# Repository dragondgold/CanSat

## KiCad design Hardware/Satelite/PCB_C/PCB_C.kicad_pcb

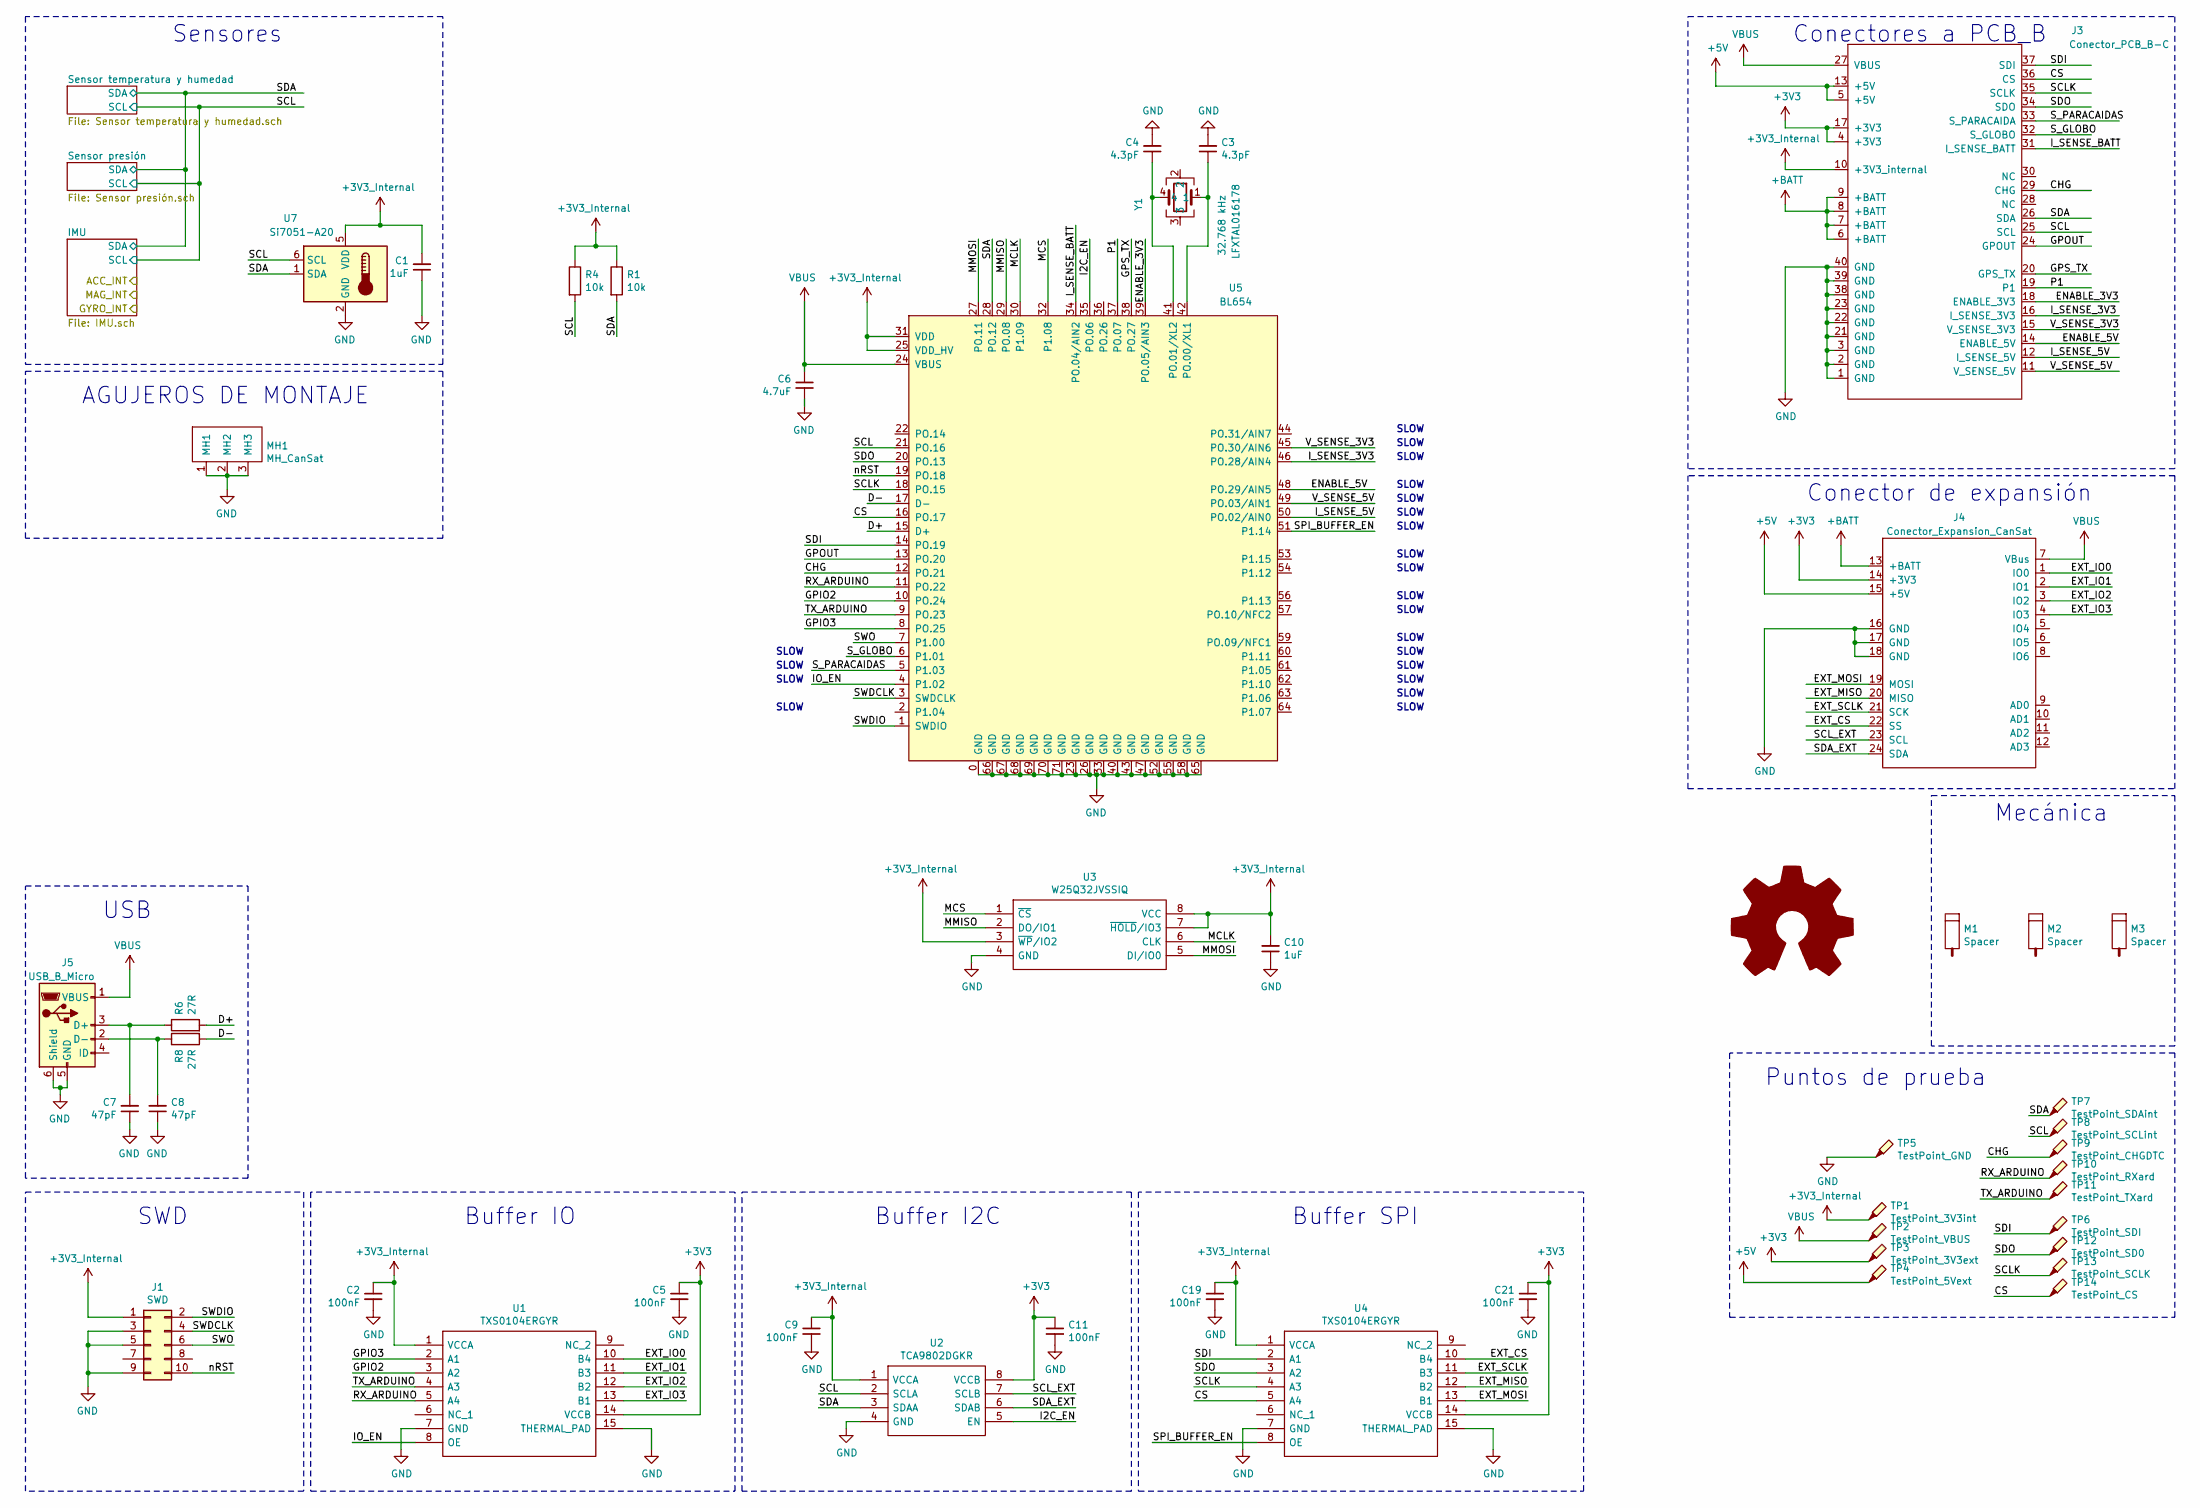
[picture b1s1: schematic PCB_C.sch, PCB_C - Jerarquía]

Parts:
C1, C10: 1uF; C_0402_1005Metric; Manufacturer Part Number GRM155R61E105KA12D
C2, C5, C9, C11, C19, C21: 100nF; C_0402_1005Metric; Manufacturer Part Number GCM155R71C104KA55D
C3, C4: 4.3pF; C_0402_1005Metric; Manufacturer Part Number GRM1555C1H4R3WA01D
C6: 4.7uF; C_0805_2012Metric_Pad1.15x1.40mm_HandSolder; Manufacturer Part Number GRM21BR71A475KE51K
C7, C8: 47pF; C_0402_1005Metric; Manufacturer Part Number AC0402JRNPO9BN470
J1: SWD; PinHeader_2x05_P1.27mm_Vertical_SMD; Manufacturer Part Number 20021121-00010D4LF
J3: Conector_PCB_B-C; Conector_PCB_B-C_Lado_C; Manufacturer Part Number 53353-1071
J4: Conector_Expansion_CanSat; Manufacturer Part Number SSQ-106-03-T-S
J5: USB_B_Micro; USB_Micro-B_Molex_47346-0001; Manufacturer Part Number 47346-1001
M1, M2, M3: Spacer; Empty_Footprint; Manufacturer Part Number R30-3010702
MH1: MH_CanSat
R1, R4: 10k; R_0603_1608Metric_Pad1.05x0.95mm_HandSolder; Manufacturer Part Number RC0603JR-0710KL
R6, R8: 27R; R_0603_1608Metric_Pad1.05x0.95mm_HandSolder; Manufacturer Part Number RC0603FR-0727RL
TP1: TestPoint_3V3int; TestPoint_Pad_D1.5mm
TP2: TestPoint_VBUS; TestPoint_Pad_D1.5mm
TP3: TestPoint_3V3ext; TestPoint_Pad_D1.5mm
TP4: TestPoint_5Vext; TestPoint_Pad_D1.5mm
TP5: TestPoint_GND; TestPoint_THTPad_1.5x1.5mm_Drill0.7mm
TP6: TestPoint_SDI; TestPoint_Pad_D1.5mm
TP7: TestPoint_SDAint; TestPoint_Pad_D1.5mm
TP8: TestPoint_SCLint; TestPoint_Pad_D1.5mm
TP9: TestPoint_CHGDTC; TestPoint_Pad_D1.5mm
TP10: TestPoint_RXard; TestPoint_Pad_D1.5mm
TP11: TestPoint_TXard; TestPoint_Pad_D1.5mm
TP12: TestPoint_SD0; TestPoint_Pad_D1.5mm
TP13: TestPoint_SCLK; TestPoint_Pad_D1.5mm
TP14: TestPoint_CS; TestPoint_Pad_D1.5mm
U1, U4: TXS0104ERGYR; Texas_S-PVQFN-N14; Manufacturer Part Number TXS0104ERGYR
U2: TCA9802DGKR; SOP65P490X110-8N; Manufacturer Part Number TCA9802DGKR
U3: W25Q32JVSSIQ; SOIC-8_3.9x4.9mm_P1.27mm; Manufacturer Part Number W25Q32JVSSIQ
U5: BL654; 45100001; Manufacturer Part Number 451-00002
U7: Si7051-A20; DFN-6-1EP_3x3mm_P1mm_EP1.5x2.4mm; Manufacturer Part Number SI7051-A20-IM
Y1: LFXTAL016178; LFXTAL016178_1; Manufacturer Part Number LFXTAL016178

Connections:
+3V3: C5.1, C11.1, C21.1, J3.4 (+3V3), J3.17 (+3V3), J4.14 (+3V3), TP3.1, U1.14 (VCCB), U2.8 (VCCB), U4.14 (VCCB)
+3V3_Internal: C1.2, C2.1, C9.1, C10.2, C19.1, J1.1, J3.10 (+3V3_internal), R1.1, R4.1, TP1.1, U1.1 (VCCA), U2.1 (VCCA), U3.3 (~WP~/IO2), U3.7 (~HOLD~/IO3), U3.8 (VCC), U4.1 (VCCA), U5.25 (VDD_HV), U5.31 (VDD), U7.5 (VDD); also elsewhere on the board
+5V: J3.5 (+5V), J3.13 (+5V), J4.15 (+5V), TP4.1
+BATT: J3.6 (+BATT), J3.7 (+BATT), J3.8 (+BATT), J3.9 (+BATT), J4.13 (+BATT)
/CHG: J3.29 (CHG), TP9.1, U5.12 (PO.21)
/CS: J3.36 (CS), TP14.1, U4.5 (A4), U5.16 (PO.17)
/D+: R6.2, U5.15 (D+)
/D-: R8.2, U5.17 (D-)
/ENABLE_3V3: J3.18 (ENABLE_3V3), U5.39 (PO.05/AIN3)
/ENABLE_5V: J3.14 (ENABLE_5V), U5.48 (PO.29/AIN5)
/EXT_CS: J4.22 (SS), U4.10 (B4)
/EXT_IO0: J4.1 (IO0), U1.10 (B4)
/EXT_IO1: J4.2 (IO1), U1.11 (B3)
/EXT_IO2: J4.3 (IO2), U1.12 (B2)
/EXT_IO3: J4.4 (IO3), U1.13 (B1)
/EXT_MISO: J4.20 (MISO), U4.12 (B2)
/EXT_MOSI: J4.19 (MOSI), U4.13 (B1)
/EXT_SCLK: J4.21 (SCK), U4.11 (B3)
/GPIO2: U1.3 (A2), U5.10 (PO.24)
/GPIO3: U1.2 (A1), U5.8 (PO.25)
/GPOUT: J3.24 (GPOUT), U5.13 (PO.20)
/GPS_TX: J3.20 (GPS_TX), U5.38 (PO.27)
/I2C_EN: U2.5 (EN), U5.35 (PO.06)
/IO_EN: U1.8 (OE), U5.4 (P1.02)
/I_SENSE_3V3: J3.16 (I_SENSE_3V3), U5.46 (PO.28/AIN4)
/I_SENSE_5V: J3.12 (I_SENSE_5V), U5.50 (PO.02/AIN0)
/I_SENSE_BATT: J3.31 (I_SENSE_BATT), U5.34 (PO.04/AIN2)
/MCLK: U3.6 (CLK), U5.30 (P1.09)
/MCS: U3.1 (~CS), U5.32 (P1.08)
/MMISO: U3.2 (DO/IO1), U5.29 (PO.08)
/MMOSI: U3.5 (DI/IO0), U5.27 (PO.11)
/P1: J3.19 (P1), U5.37 (PO.07)
/RX_ARDUINO: TP10.1, U1.5 (A4), U5.11 (PO.22)
/SCL: J3.25 (SCL), R4.2, TP8.1, U2.2 (SCLA), U5.21 (PO.16), U7.6 (SCL); also elsewhere on the board
/SCLK: J3.35 (SCLK), TP13.1, U4.4 (A3), U5.18 (PO.15)
/SCL_EXT: J4.23 (SCL), U2.7 (SCLB)
/SDA: J3.26 (SDA), R1.2, TP7.1, U2.3 (SDAA), U5.28 (PO.12), U7.1 (SDA); also elsewhere on the board
/SDA_EXT: J4.24 (SDA), U2.6 (SDAB)
/SDI: J3.37 (SDI), TP6.1, U4.2 (A1), U5.14 (PO.19)
/SDO: J3.34 (SDO), TP12.1, U4.3 (A2), U5.20 (PO.13)
/SPI_BUFFER_EN: U4.8 (OE), U5.51 (P1.14)
/SWDCLK: J1.4, U5.3 (SWDCLK)
/SWDIO: J1.2, U5.1 (SWDIO)
/SWO: J1.6, U5.7 (P1.00)
/S_GLOBO: J3.32 (S_GLOBO), U5.6 (P1.01)
/S_PARACAIDAS: J3.33 (S_PARACAIDA), U5.5 (P1.03)
/TX_ARDUINO: TP11.1, U1.4 (A3), U5.9 (PO.23)
/V_SENSE_3V3: J3.15 (V_SENSE_3V3), U5.45 (PO.30/AIN6)
/V_SENSE_5V: J3.11 (V_SENSE_5V), U5.49 (PO.03/AIN1)
/nRST: J1.10, U5.19 (PO.18)
GND: C1.1, C2.2, C3.2, C4.2, C5.2, C6.2, C7.1, C8.1, C9.2, C10.1, C11.2, C19.2, C21.2, J1.3, J1.5, J1.9, J3.1 (GND), J3.2 (GND), J3.3 (GND), J3.21 (GND), J3.22 (GND), J3.23 (GND), J3.38 (GND), J3.39 (GND), J3.40 (GND), J4.16 (GND), J4.17 (GND), J4.18 (GND), J5.5 (GND), J5.6 (Shield), MH1.1 (MH1), MH1.2 (MH2), MH1.3 (MH3), TP5.1, U1.7 (GND), U1.15 (THERMAL_PAD), U2.4 (GND), U3.4 (GND), U4.7 (GND), U4.15 (THERMAL_PAD), U5.0 (GND), U5.23 (GND), U5.26 (GND), U5.33 (GND), U5.40 (GND), U5.43 (GND), U5.47 (GND), U5.52 (GND), U5.55 (GND), U5.58 (GND), U5.65 (GND), U5.66 (GND), U5.67 (GND), U5.68 (GND), U5.69 (GND), U5.70 (GND), U5.71 (GND), U7.2 (GND); also elsewhere on the board
unnamed: C3.1, U5.42 (PO.00/XL1), Y1.1
unnamed: C4.1, U5.41 (PO.01/XL2), Y1.4
unnamed: C7.2, J5.3 (D+), R6.1
unnamed: C8.2, J5.2 (D-), R8.1
VBUS: C6.1, J3.27 (VBUS), J4.7 (VBus), J5.1 (VBUS), TP2.1, U5.24 (VBUS)

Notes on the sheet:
USB
Sensores
Buffer SPI
Buffer I2C
Buffer IO
Conectores a PCB_B
Conector de expansión
Mecánica
Puntos de prueba
SLOW
AGUJEROS DE MONTAJE
SWD

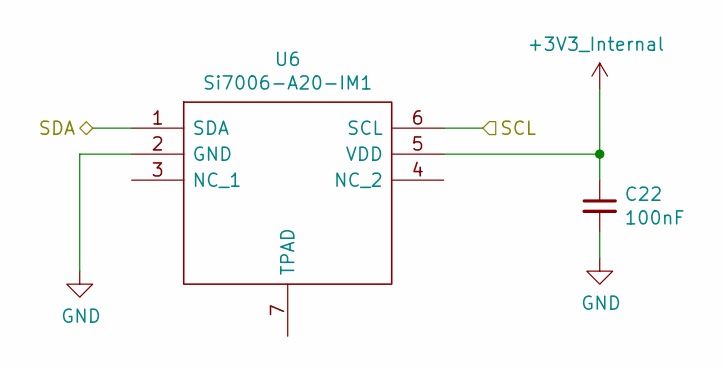
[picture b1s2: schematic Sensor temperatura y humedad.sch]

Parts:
C22: 100nF; C_0402_1005Metric; Manufacturer Part Number GCM155R71C104KA55D
U6: Si7006-A20-IM1; SON100P300X300X80-7N; Manufacturer Part Number Si7006-A20-IM1

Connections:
+3V3_Internal: C22.1, U6.5 (VDD); also elsewhere on the board
/SCL: U6.6 (SCL); also elsewhere on the board
/SDA: U6.1 (SDA); also elsewhere on the board
GND: C22.2, U6.2 (GND); also elsewhere on the board

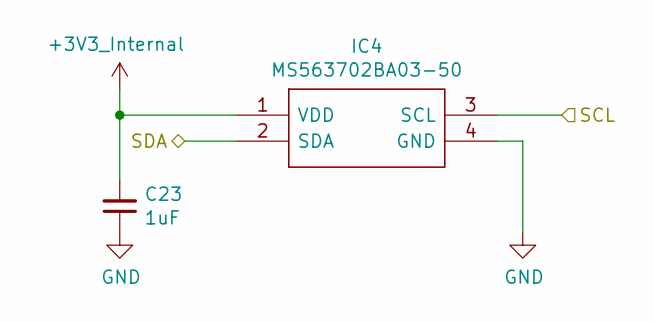
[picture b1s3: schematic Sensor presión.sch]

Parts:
C23: 1uF; C_0402_1005Metric; Manufacturer Part Number GRM155R61E105KA12D
IC4: MS563702BA03-50; MS5637_1; Manufacturer Part Number MS563702BA03-50

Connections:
+3V3_Internal: C23.2, IC4.1 (VDD); also elsewhere on the board
/SCL: IC4.3 (SCL); also elsewhere on the board
/SDA: IC4.2 (SDA); also elsewhere on the board
GND: C23.1, IC4.4 (GND); also elsewhere on the board

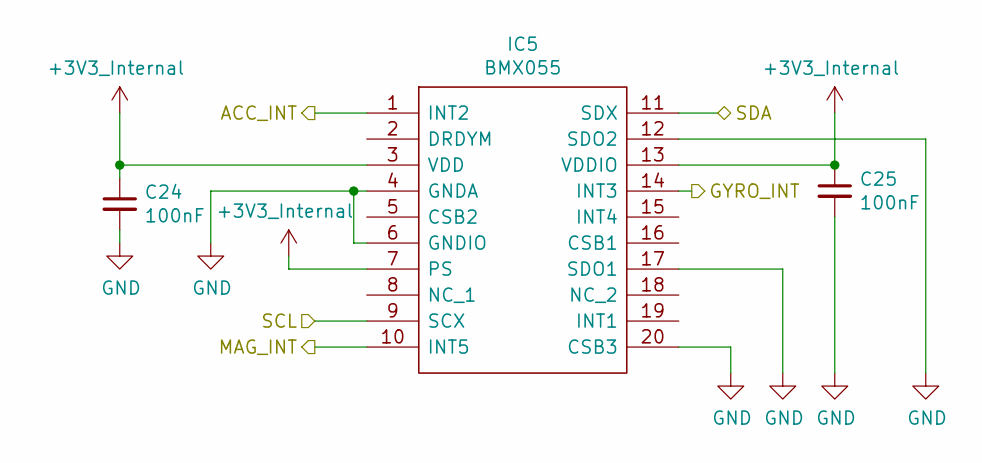
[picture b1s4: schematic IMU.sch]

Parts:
C24, C25: 100nF; C_0402_1005Metric; Manufacturer Part Number GCM155R71C104KA55D
IC5: BMX055; LGA_PACKAGE_20_PINS; Manufacturer Part Number BMX055

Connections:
+3V3_Internal: C24.1, C25.1, IC5.3 (VDD), IC5.7 (PS), IC5.13 (VDDIO); also elsewhere on the board
/IMU/ACC_INT: IC5.1 (INT2)
/IMU/GYRO_INT: IC5.14 (INT3)
/IMU/MAG_INT: IC5.10 (INT5)
/SCL: IC5.9 (SCX); also elsewhere on the board
/SDA: IC5.11 (SDX); also elsewhere on the board
GND: C24.2, C25.2, IC5.4 (GNDA), IC5.6 (GNDIO), IC5.12 (SDO2), IC5.17 (SDO1), IC5.20 (CSB3); also elsewhere on the board

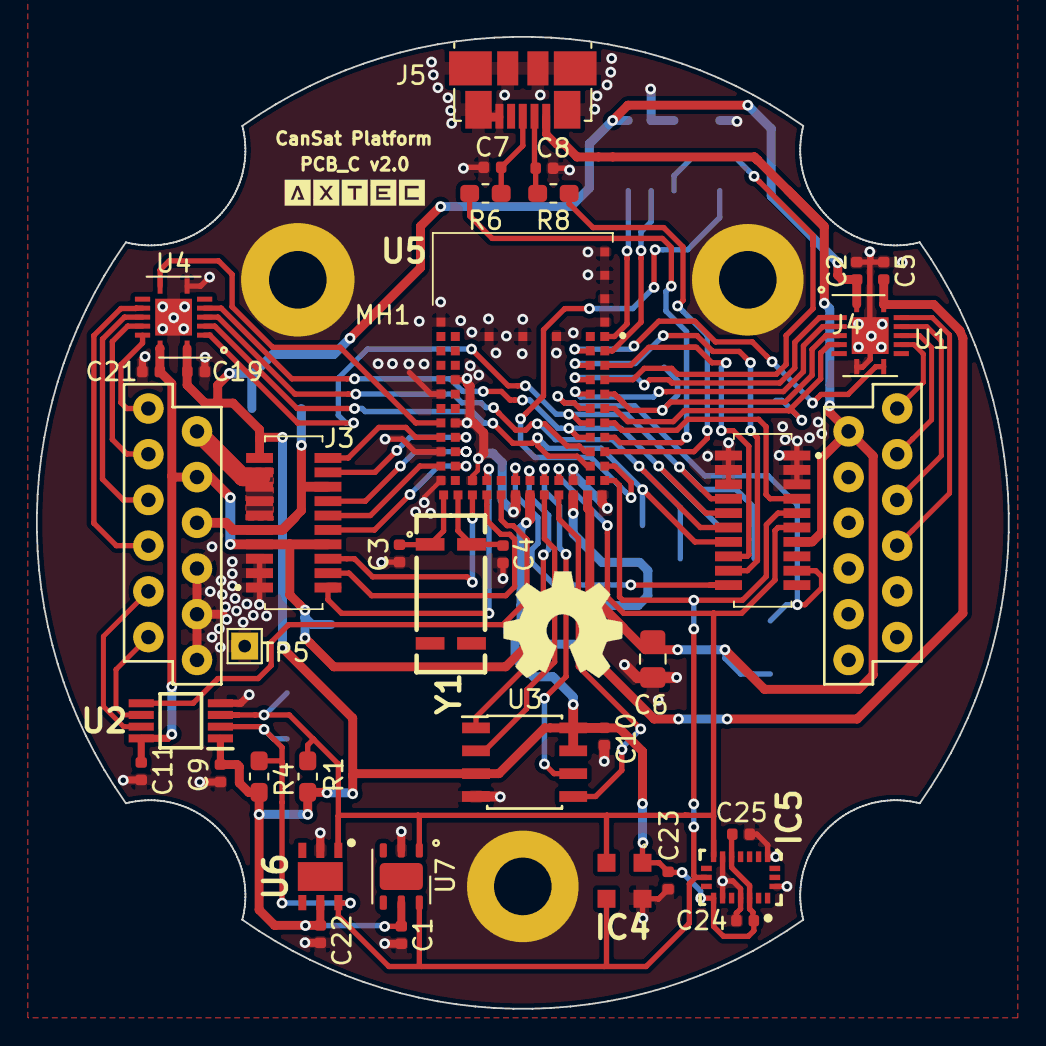
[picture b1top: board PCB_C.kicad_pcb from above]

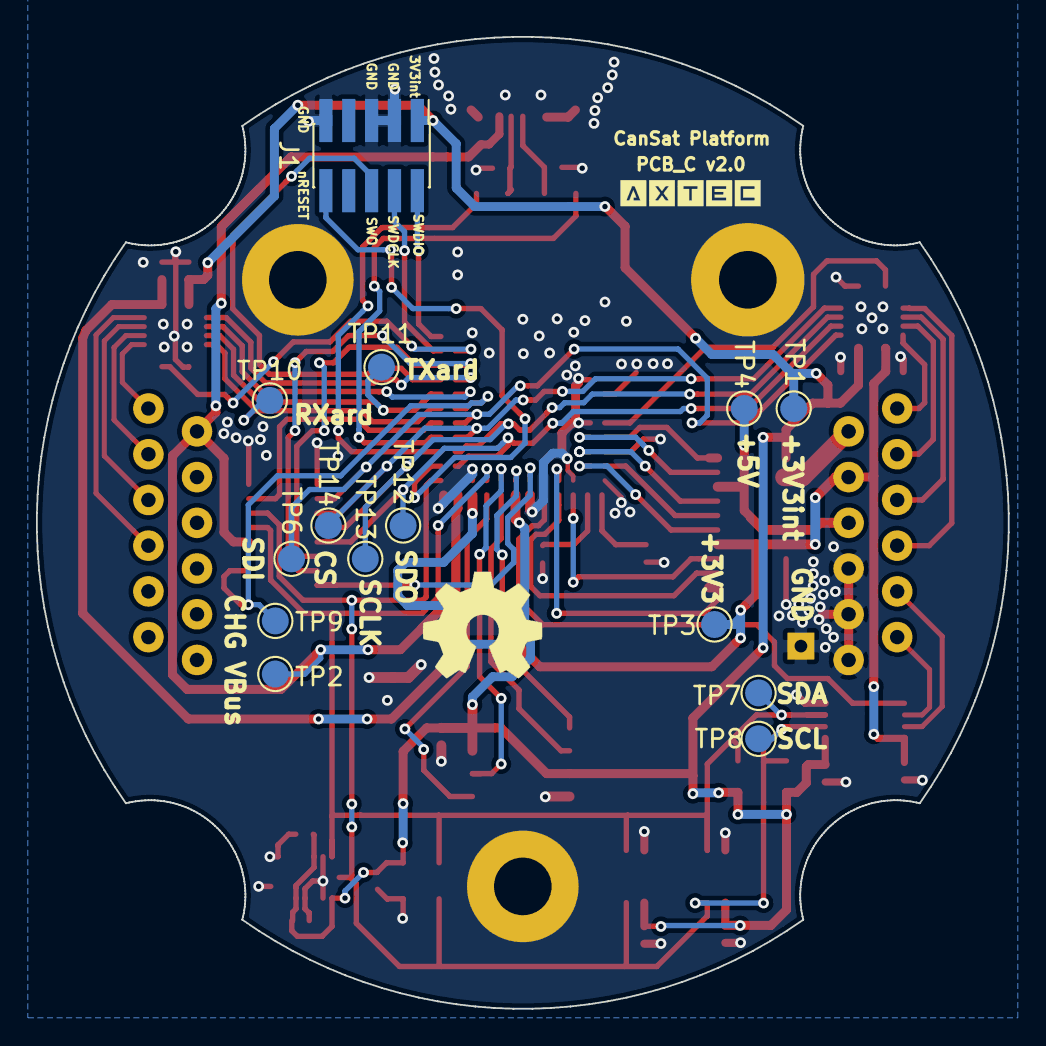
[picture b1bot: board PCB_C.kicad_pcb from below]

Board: 2 copper layers, 54.0 x 54.0 mm, 53 parts (14 on the bottom side), 56 nets.

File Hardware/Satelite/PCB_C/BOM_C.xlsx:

Qty | Reference(s) | Value | Footprint | Manufacturer Part Number
3 | C1, C10, C23 | 1uF | Capacitor_SMD:C_0402_1005Metric | GRM155R61E105KA12D
9 | C2, C5, C9, C11, C19, C21, C22, C24, C25 | 100nF | Capacitor_SMD:C_0402_1005Metric | GCM155R71C104KA55D
2 | C3, C4 | 4.3pF | Capacitor_SMD:C_0402_1005Metric | GRM1555C1H4R3WA01D
1 | C6 | 4.7uF | Capacitor_SMD:C_0805_2012Metric_Pad1.15x1.40mm_HandSolder | GRM21BR71A475KE51K
2 | C7, C8 | 47pF | Capacitor_SMD:C_0402_1005Metric | AC0402JRNPO9BN470
1 | IC4 | MS563702BA03-50 | SamacSys_Parts:MS5637_1 | MS563702BA03-50
1 | IC5 | BMX055 | SamacSys_Parts:LGA_PACKAGE_20_PINS | BMX055
1 | J1 | SWD | Connector_PinHeader_1.27mm:PinHeader_2x05_P1.27mm_Vertical_SMD | 20021121-00010D4LF
1 | J3 | Conector_PCB_B-C | AXTEC:Conector_PCB_B-C_Lado_C | 53353-1071
1 | J4 | Conector_Expansion_CanSat | AXTEC:Conector_Expansion_CanSat | SSQ-106-03-T-S
1 | J5 | USB_B_Micro | Connector_USB:USB_Micro-B_Molex_47346-0001 | 47346-1001
3 | M1, M2, M3 | Spacer | AXTEC:Empty_Footprint | R30-3010702
1 | MH1 | MH_CanSat | AXTEC:MH_CanSat
2 | R1, R4 | 10k | Resistor_SMD:R_0603_1608Metric_Pad1.05x0.95mm_HandSolder | RC0603JR-0710KL
2 | R6, R8 | 27R | Resistor_SMD:R_0603_1608Metric_Pad1.05x0.95mm_HandSolder | RC0603FR-0727RL
2 | U1, U4 | TXS0104ERGYR | Package_DFN_QFN:Texas_S-PVQFN-N14 | TXS0104ERGYR
1 | U2 | TCA9802DGKR | SamacSys_Parts:SOP65P490X110-8N | TCA9802DGKR
1 | U3 | W25Q32JVSSIQ | Package_SO:SOIC-8_3.9x4.9mm_P1.27mm | W25Q32JVSSIQ
1 | U5 | BL654 | SamacSys_Parts:45100001 | 451-00002
1 | U6 | Si7006-A20-IM1 | SamacSys_Parts:SON100P300X300X80-7N | Si7006-A20-IM1
1 | U7 | Si7051-A20 | Package_DFN_QFN:DFN-6-1EP_3x3mm_P1mm_EP1.5x2.4mm | SI7051-A20-IM
1 | Y1 | LFXTAL016178 | SamacSys_Parts:LFXTAL016178_1 | LFXTAL016178

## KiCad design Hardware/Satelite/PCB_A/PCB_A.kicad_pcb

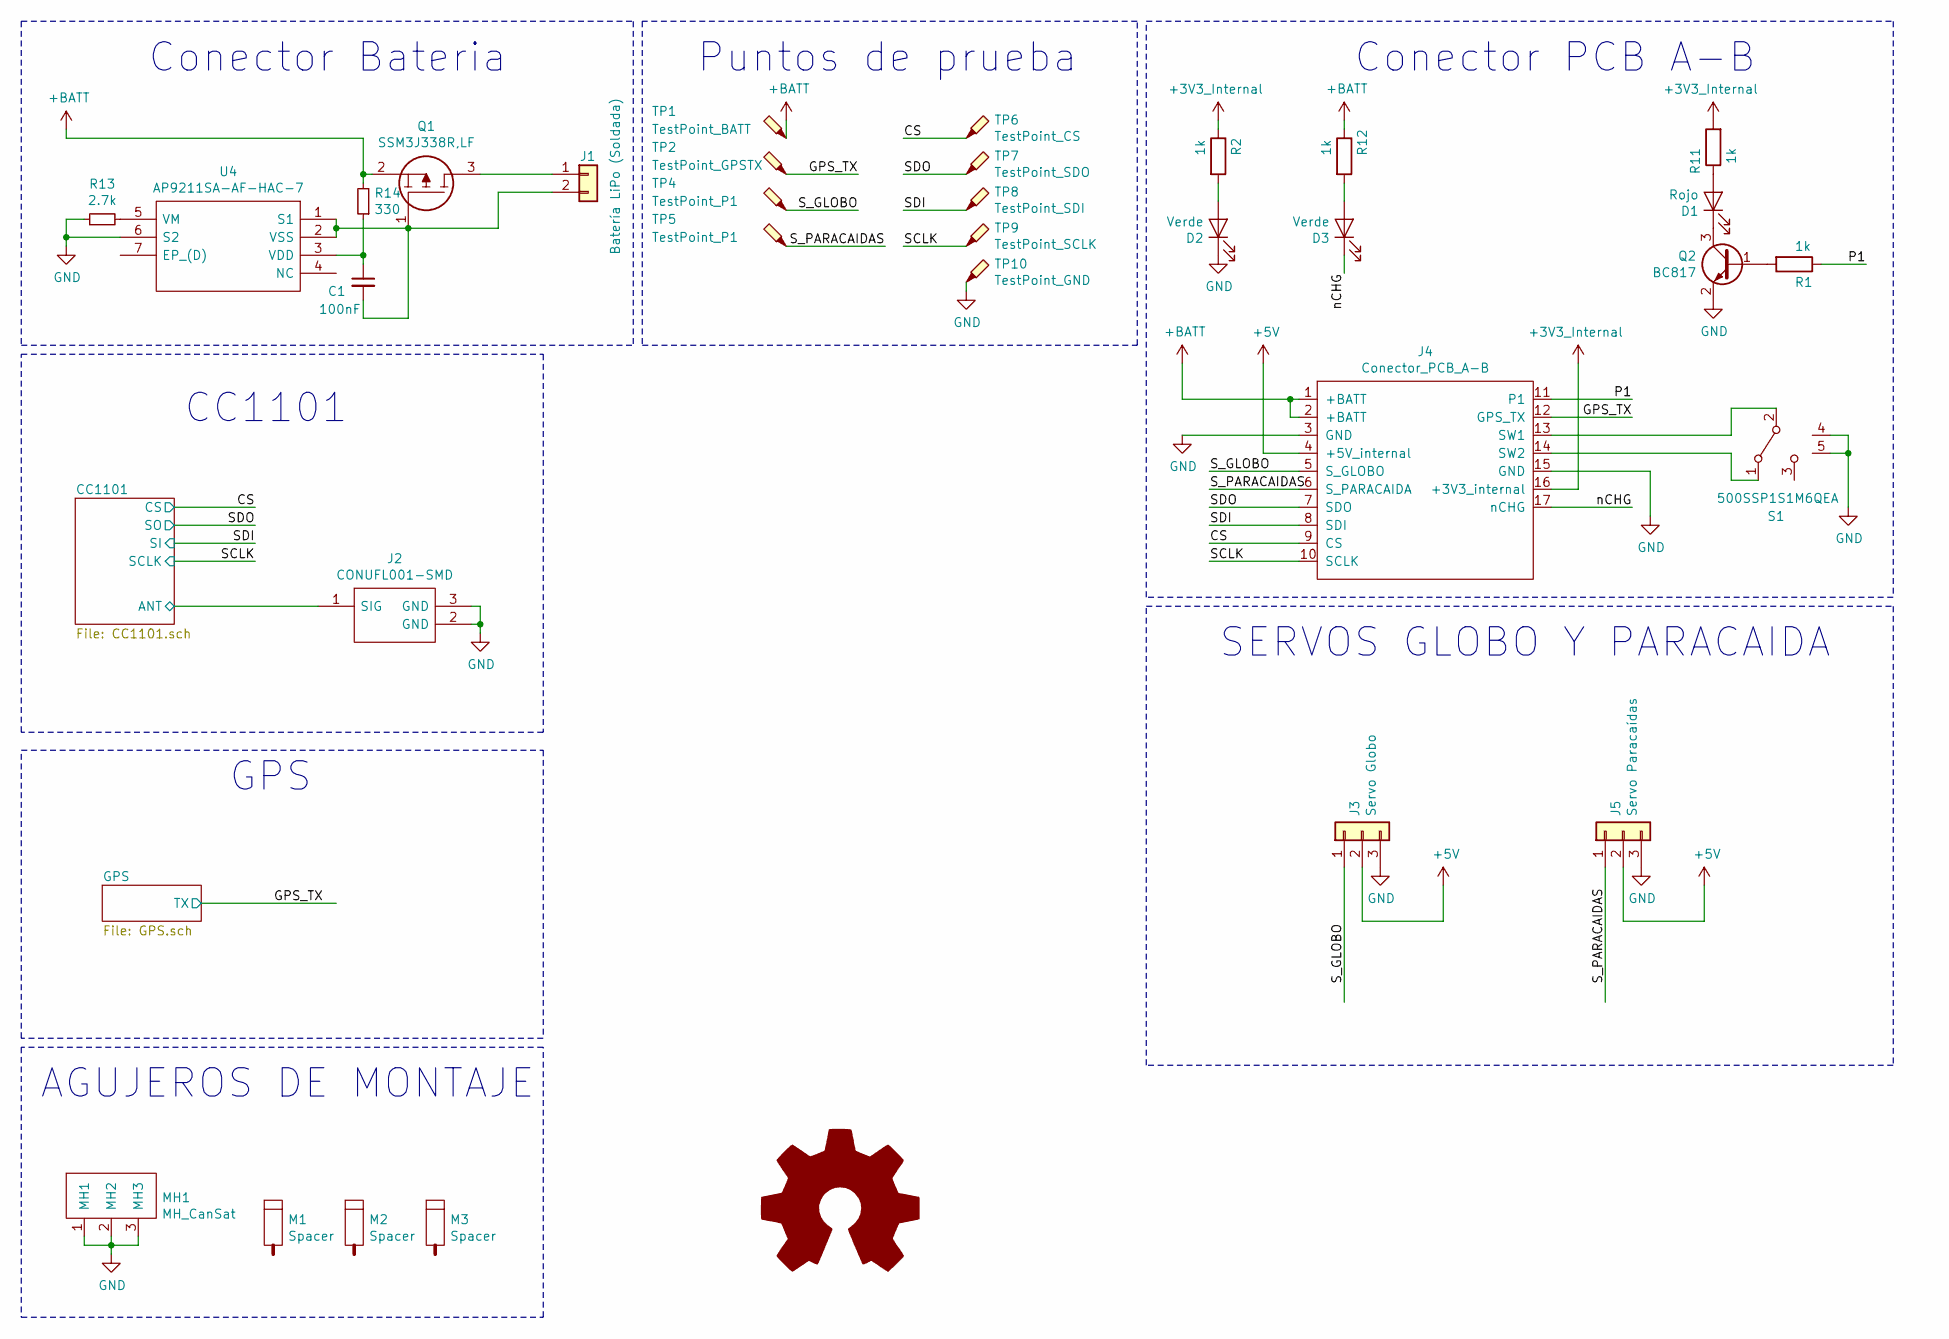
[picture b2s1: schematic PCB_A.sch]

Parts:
C1: 100nF; C_0402_1005Metric; Manufacturer Part Number GCM155R71C104KA55D
D1: Rojo; LED_0603_1608Metric_Pad1.05x0.95mm_HandSolder; Manufacturer Part Number 150060RS75000
D2, D3: Verde; LED_0603_1608Metric_Pad1.05x0.95mm_HandSolder; Manufacturer Part Number 150060VS75000
J1: Batería LiPo (Soldada); PinHeader_1x02_P2.54mm_Vertical
J2: CONUFL001-SMD; Manufacturer Part Number CONUFL001-SMD
J3: Servo Globo; PinHeader_1x03_P2.54mm_Vertical
J4: Conector_PCB_A-B; Manufacturer Part Number 22-28-5034
J5: Servo Paracaídas; PinHeader_1x03_P2.54mm_Vertical
M1, M2, M3: Spacer; Empty_Footprint; Manufacturer Part Number R30-3011002
MH1: MH_CanSat
Q1: SSM3J338R,LF; SSM3J332RLFT; Manufacturer Part Number SSM3J338R,LF
Q2: BC817; SOT-23; Manufacturer Part Number BC817-16LT1G
R1, R2, R11, R12: 1k; R_0603_1608Metric_Pad1.05x0.95mm_HandSolder; Manufacturer Part Number RC0603JR-071KL
R13: 2.7k; R_0603_1608Metric_Pad1.05x0.95mm_HandSolder; Manufacturer Part Number RC0603FR-072K7L
R14: 330; R_0603_1608Metric_Pad1.05x0.95mm_HandSolder; Manufacturer Part Number RC0603FR-07330RL
S1: 500SSP1S1M6QEA; Manufacturer Part Number 500SSP1S1M6QEA
TP1: TestPoint_BATT; TestPoint_Pad_D1.0mm
TP2: TestPoint_GPSTX; TestPoint_Pad_D1.0mm
TP4, TP5: TestPoint_P1; TestPoint_Pad_D1.0mm
TP6: TestPoint_CS; TestPoint_Pad_D1.0mm
TP7: TestPoint_SDO; TestPoint_Pad_D1.0mm
TP8: TestPoint_SDI; TestPoint_Pad_D1.0mm
TP9: TestPoint_SCLK; TestPoint_Pad_D1.0mm
TP10: TestPoint_GND; TestPoint_THTPad_1.0x1.0mm_Drill0.5mm
U4: AP9211SA-AF-HAC-7; AP9211SAACHAC7; Manufacturer Part Number AP9211SA-AF-HAC-7

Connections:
+3V3_Internal: J4.16 (+3V3_internal), R2.1, R11.2; also elsewhere on the board
+5V: J3.2, J4.4 (+5V_internal), J5.2
+BATT: J4.1 (+BATT), J4.2 (+BATT), Q1.2, R12.1, R14.2, TP1.1
/CC1101/ANT: J2.1 (SIG); also elsewhere on the board
/CS: J4.9 (CS), TP6.1; also elsewhere on the board
/GPS_TX: J4.12 (GPS_TX), TP2.1; also elsewhere on the board
/P1: J4.11 (P1), R1.1
/SCLK: J4.10 (SCLK), TP9.1; also elsewhere on the board
/SDI: J4.8 (SDI), TP8.1; also elsewhere on the board
/SDO: J4.7 (SDO), TP7.1; also elsewhere on the board
/S_GLOBO: J3.1, J4.5 (S_GLOBO), TP4.1
/S_PARACAIDAS: J4.6 (S_PARACAIDA), J5.1, TP5.1
/nCHG: D3.1 (K), J4.17 (nCHG)
GND: D2.1 (K), J2.2 (GND), J2.3 (GND), J3.3, J4.3 (GND), J4.15 (GND), J5.3, MH1.1 (MH1), MH1.2 (MH2), MH1.3 (MH3), Q2.2 (E), R13.1, S1.4, S1.5, TP10.1, U4.6 (S2); also elsewhere on the board
unnamed: C1.1, R14.1, U4.3 (VDD)
unnamed: C1.2, J1.2, Q1.1, U4.1 (S1), U4.2 (VSS)
unnamed: D1.1 (K), Q2.3 (C)
unnamed: D1.2 (A), R11.1
unnamed: D2.2 (A), R2.2
unnamed: D3.2 (A), R12.2
unnamed: J1.1, Q1.3
unnamed: J4.13 (SW1), S1.2
unnamed: J4.14 (SW2), S1.1
unnamed: Q2.1 (B), R1.2
unnamed: R13.2, U4.5 (VM)

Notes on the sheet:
Conector PCB A-B
Conector Bateria
CC1101
SERVOS GLOBO Y PARACAIDA
GPS
AGUJEROS DE MONTAJE
Puntos de prueba

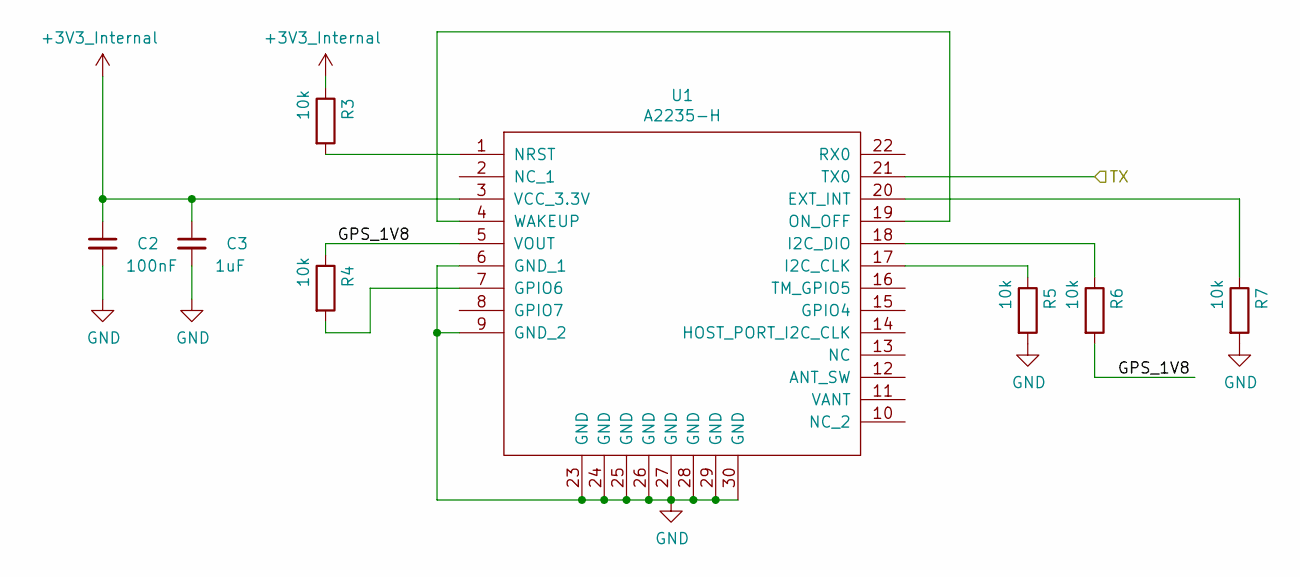
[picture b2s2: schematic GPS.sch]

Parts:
C2: 100nF; C_0402_1005Metric; Manufacturer Part Number GCM155R71C104KA55D
C3: 1uF; C_0603_1608Metric_Pad1.05x0.95mm_HandSolder; Manufacturer Part Number LMK107B7105MA-T
R3, R4, R5, R6, R7: 10k; R_0603_1608Metric_Pad1.05x0.95mm_HandSolder; Manufacturer Part Number RC0603JR-0710KL
U1: A2235-H; Manufacturer Part Number A2235-H

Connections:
+3V3_Internal: C2.1, C3.1, R3.1, U1.3 (VCC_3.3V); also elsewhere on the board
/GPS/GPS_1V8: R4.1, R6.2, U1.5 (VOUT)
/GPS_TX: U1.21 (TX0); also elsewhere on the board
GND: C2.2, C3.2, R5.2, R7.2, U1.6 (GND_1), U1.9 (GND_2), U1.23 (GND), U1.24 (GND), U1.25 (GND), U1.26 (GND), U1.27 (GND), U1.28 (GND), U1.29 (GND), U1.30 (GND); also elsewhere on the board
unnamed: R3.2, U1.1 (NRST)
unnamed: R4.2, U1.7 (GPIO6)
unnamed: R5.1, U1.17 (I2C_CLK)
unnamed: R6.1, U1.18 (I2C_DIO)
unnamed: R7.1, U1.20 (EXT_INT)
unnamed: U1.4 (WAKEUP), U1.19 (ON_OFF)

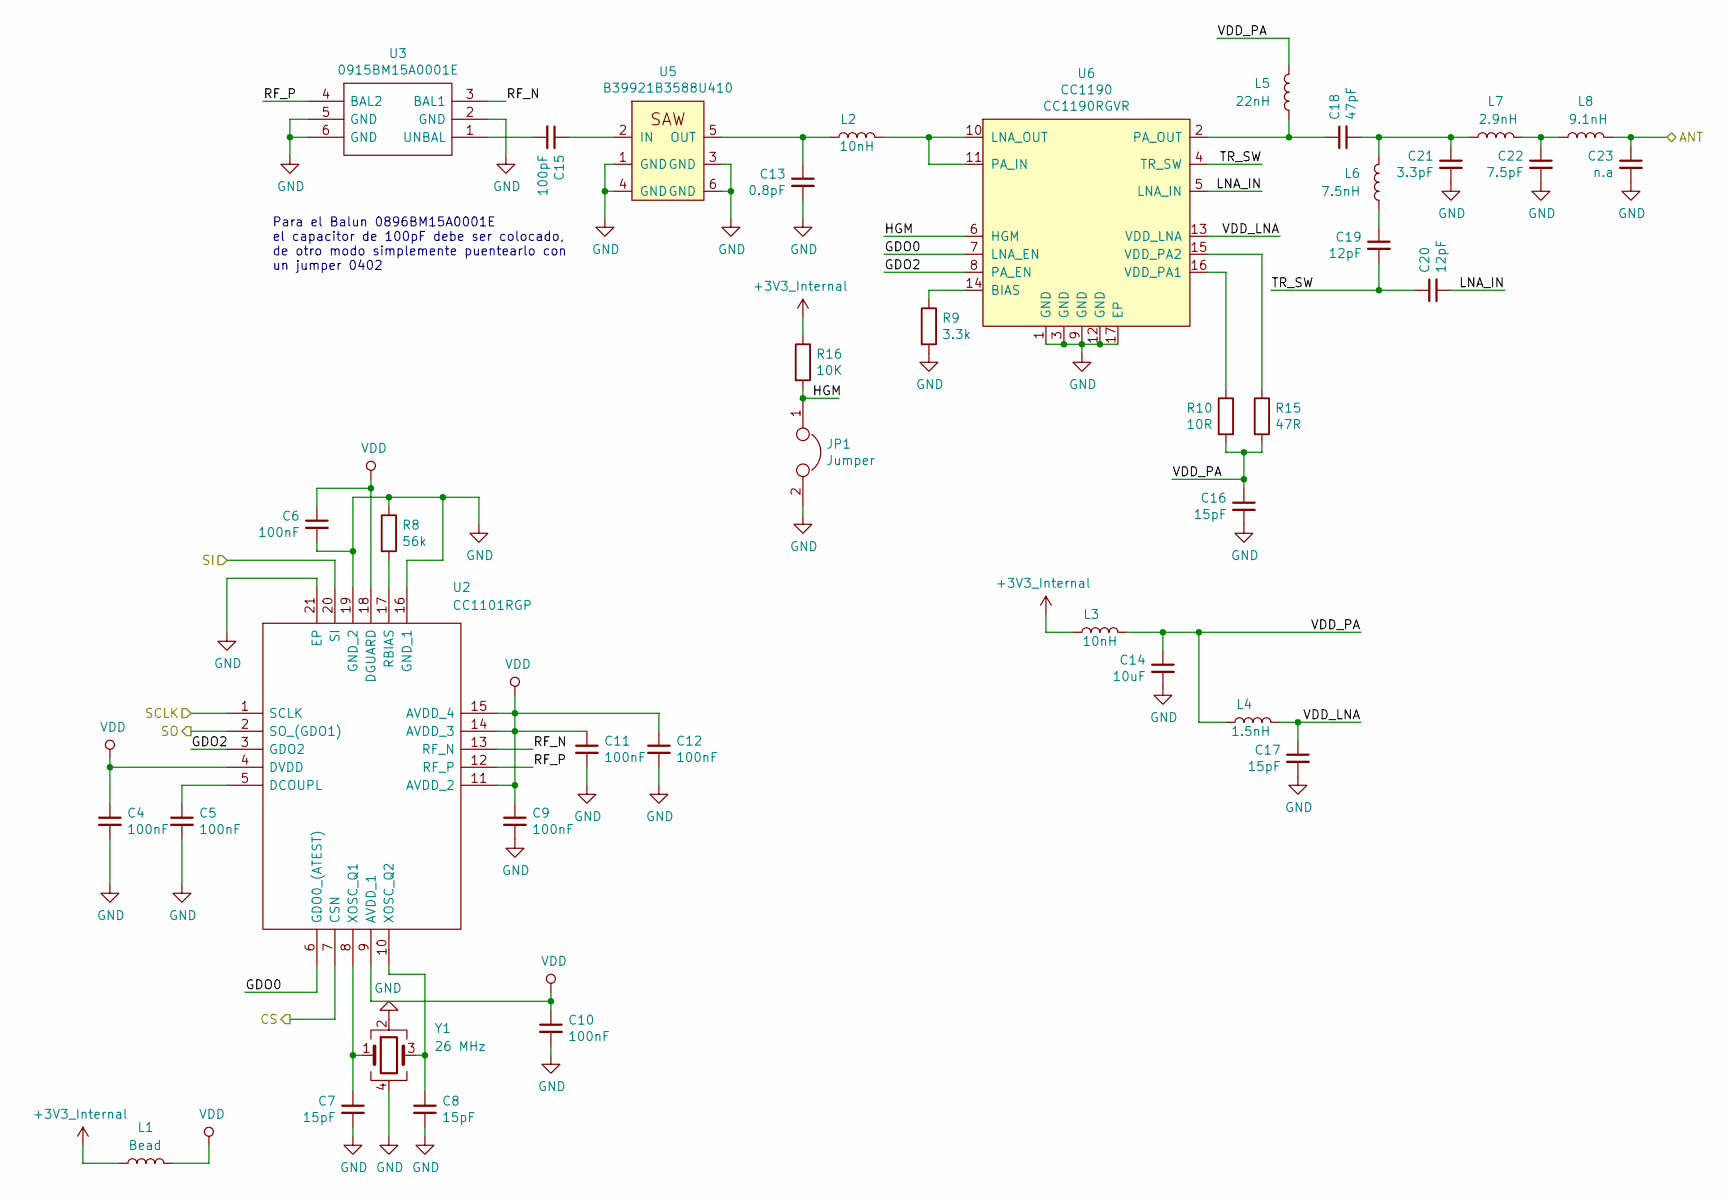
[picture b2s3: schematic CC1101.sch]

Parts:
C4, C5, C6, C9, C10, C11, C12: 100nF; C_0402_1005Metric; Voltage 16V; Manufacturer Part Number GCM155R71C104KA55D
C7, C8: 15pF; C_0402_1005Metric; Voltage 10V; Manufacturer Part Number C0402C150J5GACTU
C13: 0.8pF; C_0402_1005Metric; Manufacturer Part Number GRM1555C2AR80BA01D
C14: 10uF; C_0805_2012Metric_Pad1.15x1.40mm_HandSolder; Manufacturer Part Number C2012X7R1A106M125AC
C15: 100pF; C_0402_1005Metric; Voltage 25V; Manufacturer Part Number 885012005046
C16, C17: 15pF; C_0402_1005Metric; Manufacturer Part Number CC0402JRNPO9BN150
C18: 47pF; C_0402_1005Metric; Manufacturer Part Number GCM1555C1H470JA16J
C19, C20: 12pF; C_0402_1005Metric; Manufacturer Part Number GRM1555C1H120GA01D
C21: 3.3pF; C_0402_1005Metric; Manufacturer Part Number GJM1555C1H3R3DB01D
C22: 7.5pF; C_0402_1005Metric; Manufacturer Part Number GCM1555C1H7R5DA16D
C23: n.a; C_0402_1005Metric
JP1: Jumper; SolderJumper-2_P1.3mm_Open_RoundedPad1.0x1.5mm
L1: Bead; L_0402_1005Metric; Manufacturer Part Number BLM15HG102SN1D
L2, L3: 10nH; L_0402_1005Metric; Manufacturer Part Number LQG15HN10NH02D
L4: 1.5nH; L_0402_1005Metric; Manufacturer Part Number LQG15HS1N5S02D
L5: 22nH; L_0603_1608Metric_Pad1.05x0.95mm_HandSolder; Manufacturer Part Number LQW18AN22NJ10D
L6: 7.5nH; L_0402_1005Metric; Manufacturer Part Number LQW15AN7N5G00D
L7: 2.9nH; L_0402_1005Metric; Manufacturer Part Number LQW15AN2N9B00D
L8: 9.1nH; L_0402_1005Metric; Manufacturer Part Number LQW15AN9N1G00D
R8: 56k; R_0402_1005Metric; Manufacturer Part Number RC0402FR-0756KL
R9: 3.3k; R_0402_1005Metric; Manufacturer Part Number RC0402FR-073K3L
R10: 10R; R_0402_1005Metric; Manufacturer Part Number RC0402FR-0710RL
R15: 47R; R_0402_1005Metric; Manufacturer Part Number RC0402FR-0747RL
R16: 10K; R_0603_1608Metric_Pad1.05x0.95mm_HandSolder; Manufacturer Part Number RC0603JR-0710KL
U2: CC1101RGP; QFN50P400X400X100-21N-D; Manufacturer Part Number CC1101RGP
U3: 0915BM15A0001E; Manufacturer Part Number 0915BM15A0001E
U5: B39921B3588U410; Manufacturer Part Number B39921B3588U410
U6: CC1190; Texas_S-PVQFN-N16_EP2.7x2.7mm; Manufactuer Part Number CC1190RGVR
Y1: 26 MHz; Crystal_SMD_2520-4Pin_2.5x2.0mm; Manufacturer Part Number FA-20H 26.0000MF12V-W

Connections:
+3V3_Internal: L1.2, L3.1, R16.1; also elsewhere on the board
/CC1101/ANT: C23.1, L8.1; also elsewhere on the board
/CC1101/GDO0: U2.6 (GDO0_(ATEST)), U6.7 (LNA_EN)
/CC1101/GDO2: U2.3 (GDO2), U6.8 (PA_EN)
/CC1101/HGM: JP1.1, R16.2, U6.6 (HGM)
/CC1101/LNA_IN: C20.2, U6.5 (LNA_IN)
/CC1101/RF_N: U2.13 (RF_N), U3.3 (BAL1)
/CC1101/RF_P: U2.12 (RF_P), U3.4 (BAL2)
/CC1101/TR_SW: C19.2, C20.1, U6.4 (TR_SW)
/CC1101/VDD_LNA: C17.1, L4.2, U6.13 (VDD_LNA)
/CC1101/VDD_PA: C14.1, C16.1, L3.2, L4.1, L5.1, R10.2, R15.2
/CS: U2.7 (CSN); also elsewhere on the board
/SCLK: U2.1 (SCLK); also elsewhere on the board
/SDI: U2.20 (SI); also elsewhere on the board
/SDO: U2.2 (SO_(GDO1)); also elsewhere on the board
GND: C4.2, C5.2, C6.2, C7.2, C8.2, C9.2, C10.2, C11.2, C12.2, C13.2, C14.2, C16.2, C17.2, C21.2, C22.2, C23.2, JP1.2, R8.1, R9.2, U2.16 (GND_1), U2.19 (GND_2), U2.21 (EP), U3.2 (GND), U3.5 (GND), U3.6 (GND), U5.1 (GND), U5.3 (GND), U5.4 (GND), U5.6 (GND), U6.1 (GND), U6.3 (GND), U6.9 (GND), U6.12 (GND), U6.17 (EP), Y1.2, Y1.4; also elsewhere on the board
unnamed: C5.1, U2.5 (DCOUPL)
unnamed: C7.1, U2.8 (XOSC_Q1), Y1.1
unnamed: C8.1, U2.10 (XOSC_Q2), Y1.3
unnamed: C13.1, L2.1, U5.5 (OUT)
unnamed: C15.1, U5.2 (IN)
unnamed: C15.2, U3.1 (UNBAL)
unnamed: C18.1, L5.2, U6.2 (PA_OUT)
unnamed: C18.2, C21.1, L6.1, L7.2
unnamed: C19.1, L6.2
unnamed: C22.1, L7.1, L8.2
unnamed: L2.2, U6.10 (LNA_OUT), U6.11 (PA_IN)
unnamed: R8.2, U2.17 (RBIAS)
unnamed: R9.1, U6.14 (BIAS)
unnamed: R10.1, U6.16 (VDD_PA1)
unnamed: R15.1, U6.15 (VDD_PA2)
VDD: C4.1, C6.1, C9.1, C10.1, C11.1, C12.1, L1.1, U2.4 (DVDD), U2.9 (AVDD_1), U2.11 (AVDD_2), U2.14 (AVDD_3), U2.15 (AVDD_4), U2.18 (DGUARD)

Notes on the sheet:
Para el Balun 0896BM15A0001E el capacitor de 100pF debe ser colocado, de otro modo simplemente puentearlo con un jumper 0402
